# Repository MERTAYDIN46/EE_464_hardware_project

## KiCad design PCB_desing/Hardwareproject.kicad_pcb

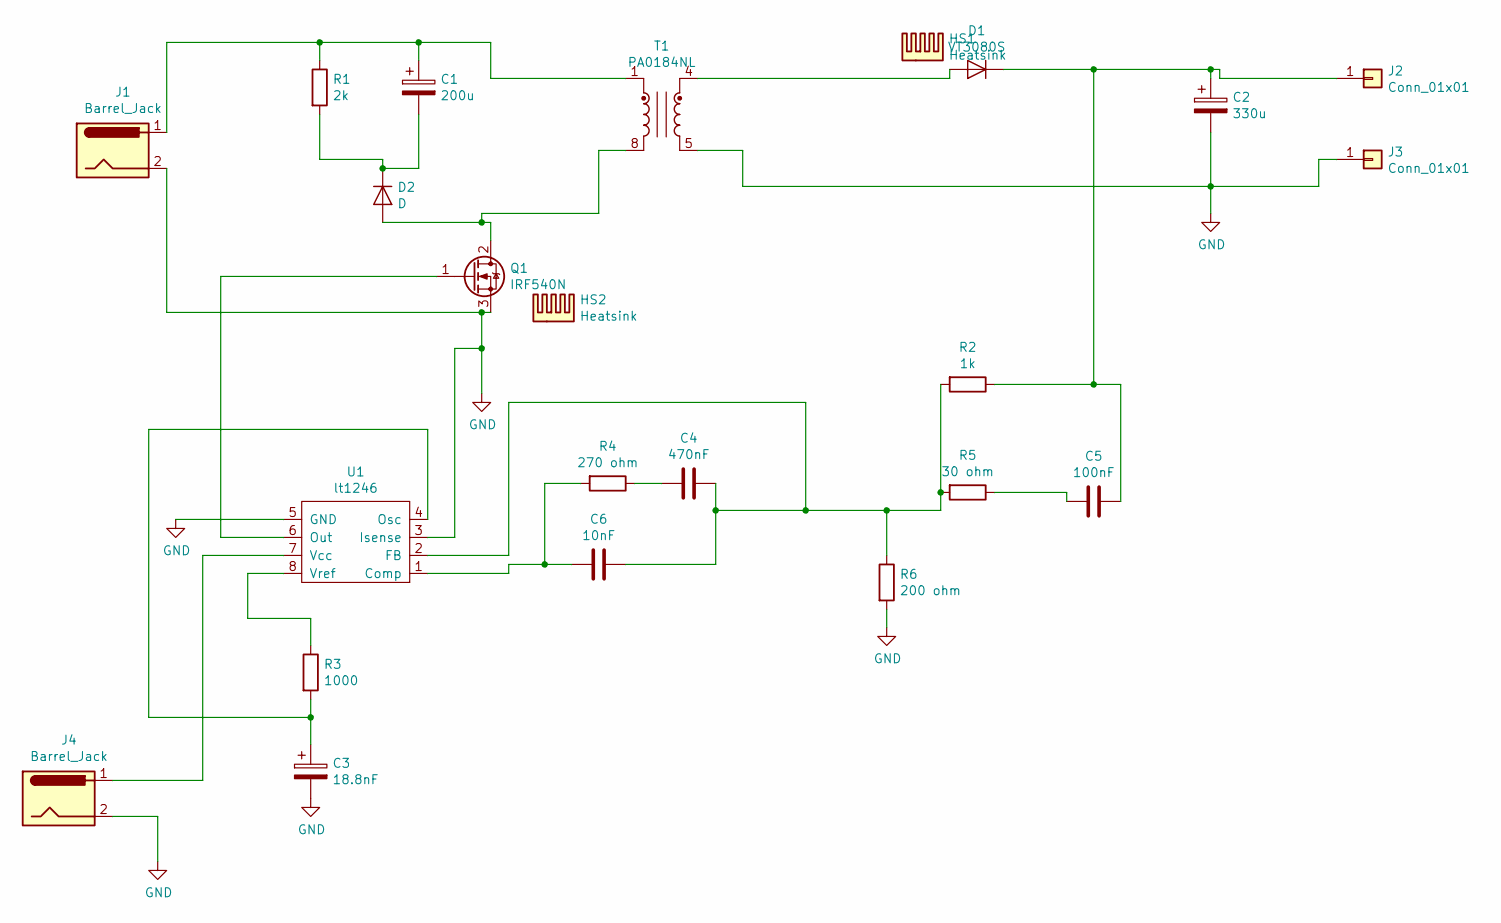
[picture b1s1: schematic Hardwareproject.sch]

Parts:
C1: 200u; CP_Radial_D7.5mm_P2.50mm
C2: 330u; CP_Radial_D12.5mm_P5.00mm
C3: 18.8nF; CP_EIA-3216-10_Kemet-I
C4: 470nF; CP_EIA-3216-10_Kemet-I
C5: 100nF; CP_EIA-3216-10_Kemet-I
C6: 10nF; CP_EIA-3216-10_Kemet-I
D1: VT3080S; TO-220-2_Vertical
D2: D; D_A-405_P7.62mm_Horizontal
HS1, HS2: Heatsink; Heatsink_Stonecold_HS-132_32x14mm_2xFixation1.5mm
J1, J4: Barrel_Jack; BarrelJack_CUI_PJ-063AH_Horizontal
J2, J3: Conn_01x01; Banana_Jack_1Pin
Q1: IRF540N; TO-220-3_Vertical
R1: 2k; R_Axial_DIN0204_L3.6mm_D1.6mm_P5.08mm_Horizontal
R2: 1k; R_Axial_DIN0204_L3.6mm_D1.6mm_P5.08mm_Horizontal
R3: 1000; R_Axial_DIN0204_L3.6mm_D1.6mm_P5.08mm_Horizontal
R4: 270 ohm; R_Axial_DIN0204_L3.6mm_D1.6mm_P5.08mm_Horizontal
R5: 30 ohm; R_Axial_DIN0204_L3.6mm_D1.6mm_P5.08mm_Horizontal
R6: 200 ohm; R_Axial_DIN0204_L3.6mm_D1.6mm_P5.08mm_Horizontal
T1: PA0184NL; Transformer_CHK_EI54-12VA_1xSec
U1: lt1246; DIP-8_W7.62mm

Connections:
GND: C2.2, C3.2, J1.2, J3.1, J4.2, Q1.3 (S), R6.2, T1.5, U1.3 (Isense), U1.5 (GND)
unnamed: C1.1, J1.1, R1.1, T1.1
unnamed: C1.2, D2.1 (K), R1.2
unnamed: C2.1, C5.1, D1.1 (K), J2.1, R2.1
unnamed: C3.1, R3.2, U1.4 (Osc)
unnamed: C4.1, C6.1, R2.2, R5.2, R6.1, U1.2 (FB)
unnamed: C4.2, R4.1
unnamed: C5.2, R5.1
unnamed: C6.2, R4.2, U1.1 (Comp)
unnamed: D1.2 (A), T1.4
unnamed: D2.2 (A), Q1.2 (D), T1.8
unnamed: J4.1, U1.7 (Vcc)
unnamed: Q1.1 (G), U1.6 (Out)
unnamed: R3.1, U1.8 (Vref)

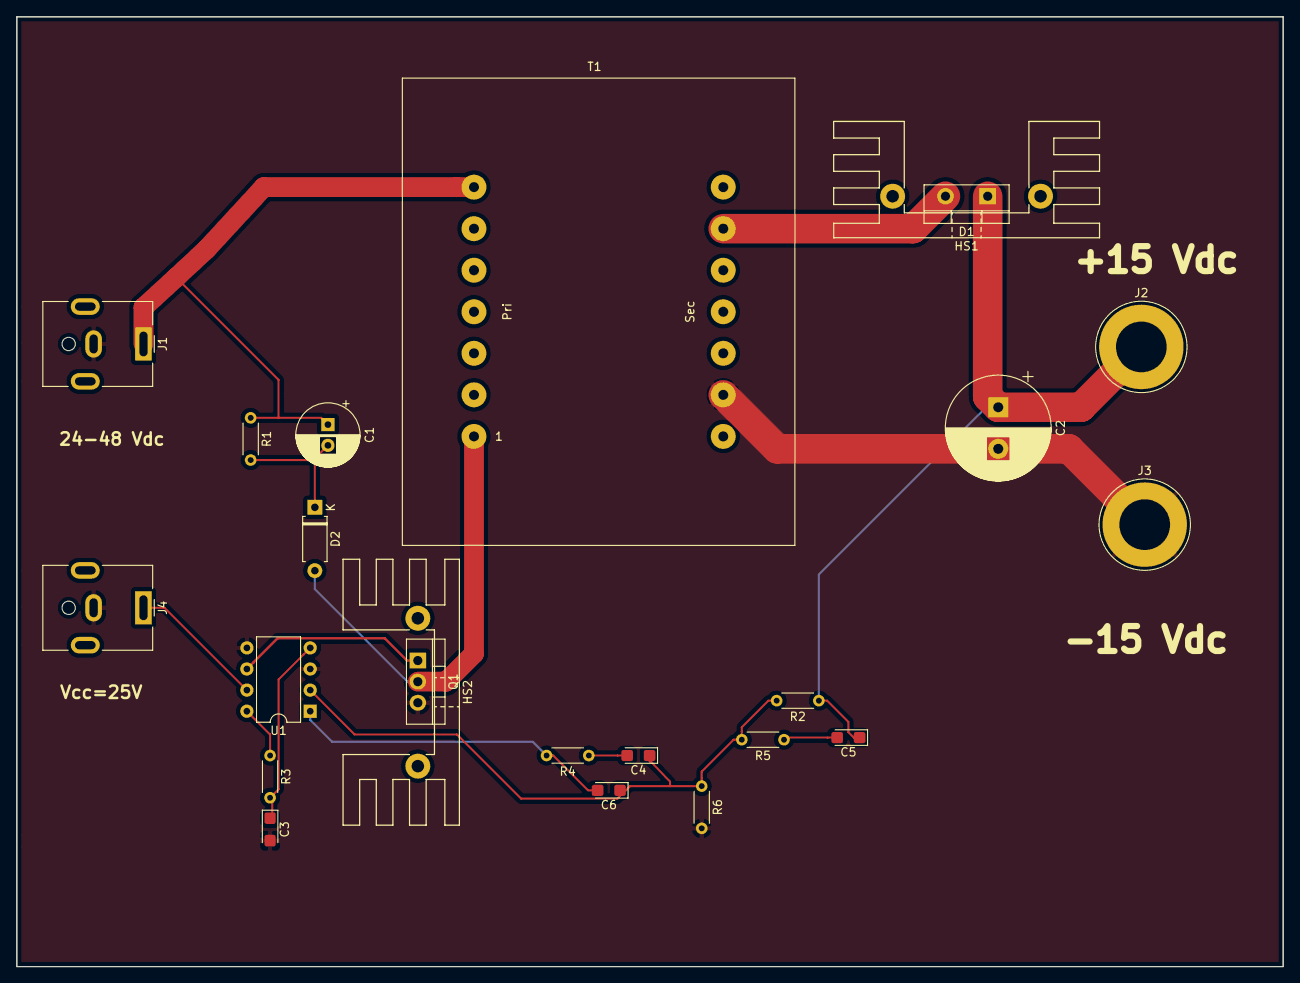
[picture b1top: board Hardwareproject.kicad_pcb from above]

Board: 2 copper layers, 152.4 x 114.3 mm, 23 parts (0 on the bottom side), 14 nets.

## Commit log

2020-03-23 Formed Flyback design tool is added
2020-03-23 Overall model.
2020-03-23 Controlle and simulation results
2020-03-23 Add files via upload
    Overleaf output of the project. Latex version also can be found in it.
2020-05-09 Bode plot has been observed
2020-06-14 schematic is defined some foot prints are also assigned to components.
2020-06-24 All PCB is done, average switch network is created and transfer function tested.
2020-06-24 All PCB work is done
2020-06-24 Report.
2020-06-24 Main circuit
2020-06-25 Final works
2020-06-25 Thermal test circuit
2020-06-25 Add files via upload
    **Due to technical problems and unexpected simulation errors, we have upload it with delay.
    EE46 hardware project final report.
2020-06-25 Add files via upload
    In case of blurred or low resolution figures, I also share the overleaf source output of the final report.
